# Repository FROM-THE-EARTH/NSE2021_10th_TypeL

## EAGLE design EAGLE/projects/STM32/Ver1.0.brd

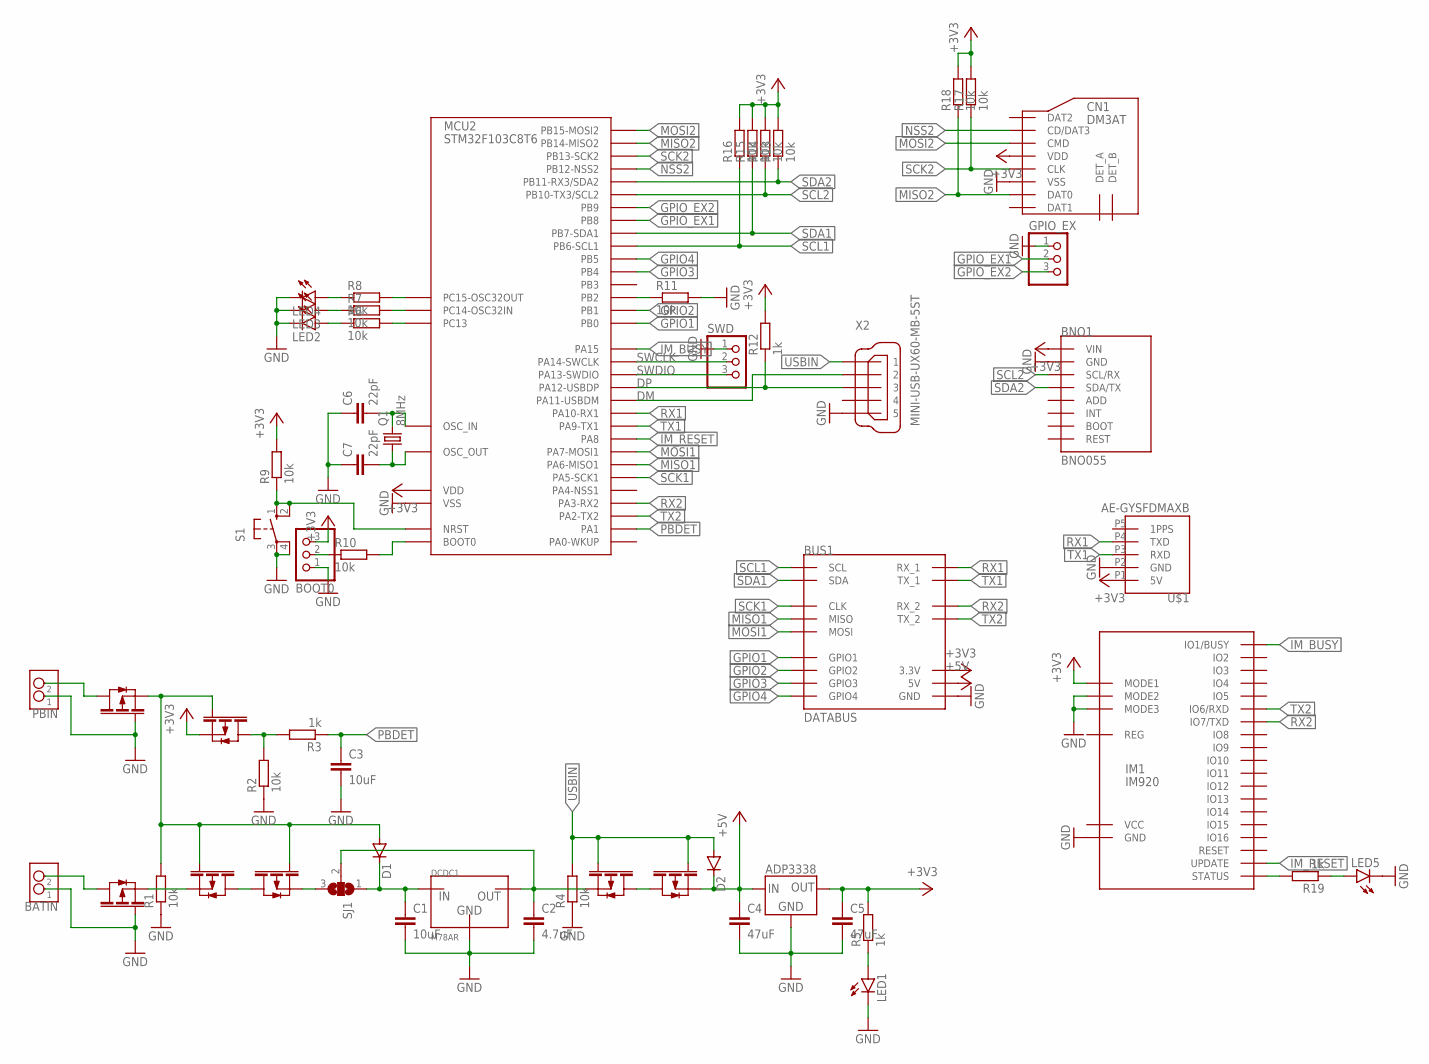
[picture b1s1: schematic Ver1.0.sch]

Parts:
BATIN: S2B-XH-A
BNO1: BNO055
BOOT0: PINHD-1X3/90; 1X03/90
BUS1: DATABUS; 8X2
C1, C3: 10uF; C2012
C2: 4.7uF; C2012
C4, C5: 47uF; C2012
C6, C7: 22pF; C2012
CN1: DM3AT
D1, D2: DIODE-SOD123; SOD123
DCDC1: M78AR
FET1, FET2, FET3, FET4, FET5, FET6, FET7: PCH; SOT-23
GPIO_EX: PINHD-1X3; 1X03
IC1: ADP3338-3.3; SOT-223
IM1: IM920
LED1, LED2, LED3, LED4, LED5: LEDSMT1206; 1206
MCU2: STM32F103C8T6; LQFP48
PBIN: S2B-XH-A
Q1: 8MHz; HC49/S
R1, R2, R4, R6, R7, R8, R9, R10, R11, R13, R14, R15, R16, R17, R18: 10k; R2012
R3, R5, R12, R19: 1k; R2012
S1: 10-XX; B3F-10XX
SJ1: SJ2W; SJ_2
SWD: PINHD-1X3/90; 1X03/90
U$1: AE-GYSFDMAXB
X2: MINI-USB-UX60-MB-5ST; UX60-MB-5ST

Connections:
+3V3: BNO1.P1 (VIN), BOOT0.3, BUS1.P6 (3.3V), CN1.VDD, FET5.P$2, IM1.IO17 (MODE1), MCU2.1 (VDD), MCU2.9 (VDD), MCU2.24 (VDD), MCU2.36 (VDD), MCU2.48 (VDD), R9.2, R12.2, R13.2, R14.2, R15.2, R16.2, R17.2, R18.2, U$1.P1 (5V)
+5V: BUS1.P7 (5V), C4.1, D2.C, FET7.P$2, IC1.3 (IN)
BAT_CON_FET: BATIN.P$2 (2), FET2.P$3
BAT_FET_FET1: FET2.P$2, FET3.P$2
BAT_FET_FET2: FET3.P$3, FET4.P$3
BAT_JMP_DCDC: C1.1, D1.C, DCDC1.P3 (IN), SJ1.1
BOOT0: MCU2.44 (BOOT0), R10.2
BOOT0_R_SEL: BOOT0.2, R10.1
DCDC_FET: C2.1, DCDC1.P1 (OUT), FET6.P$2, SJ1.2
DCDC_FET_FET: FET6.P$3, FET7.P$3
DM: MCU2.32 (PA11-USBDM), X2.2
DP: MCU2.33 (PA12-USBDP), R12.1, X2.3
GND: BATIN.P$1 (1), BNO1.P2 (GND), BOOT0.1, BUS1.P11 (GND), C1.2, C2.2, C3.2, C4.2, C5.2, C6.1, C7.1, CN1.VSS, DCDC1.P2 (GND), FET1.P$1, FET2.P$1, GPIO_EX.1, IC1.4 (GND), IM1.IO18 (MODE2), IM1.IO19 (MODE3), IM1.IO24 (GND), LED1.C, LED2.C, LED3.C, LED4.C, LED5.C, MCU2.8 (VSS), MCU2.23 (VSS), MCU2.35 (VSS), MCU2.47 (VSS), PBIN.P$1 (1), R1.1, R2.1, R4.1, R11.2, S1.3, S1.4 (P1), SWD.1, U$1.P2 (GND), X2.5
GPIO1: BUS1.P3 (GPIO1), MCU2.18 (PB0)
GPIO2: BUS1.P10 (GPIO2), MCU2.19 (PB1)
GPIO3: BUS1.P14 (GPIO3), MCU2.40 (PB4)
GPIO4: BUS1.P15 (GPIO4), MCU2.41 (PB5)
GPIO_EX1: GPIO_EX.2, MCU2.45 (PB8)
GPIO_EX2: GPIO_EX.3, MCU2.46 (PB9)
IM_BUSY: IM1.IO1 (IO1/BUSY), MCU2.38 (PA15)
IM_RESET: IM1.IO20 (UPDATE), MCU2.29 (PA8)
IM_STATUS_LED: LED5.A, R19.1
IM_STATUS_R: IM1.IO21 (STATUS), R19.2
MISO1: BUS1.P12 (MISO), MCU2.16 (PA6-MISO1)
MISO2: CN1.DAT0, MCU2.27 (PB14-MISO2), R18.1
MOSI1: BUS1.P2 (MOSI), MCU2.17 (PA7-MOSI1)
MOSI2: CN1.CMD, MCU2.28 (PB15-MOSI2)
NRST: MCU2.7 (NRST), R9.1, S1.1 (S), S1.2 (S1)
NSS2: CN1.CD/DAT3, MCU2.25 (PB12-NSS2)
OSCI_C: C6.2, MCU2.5 (OSC_IN), Q1.2
OSCO_C: C7.2, MCU2.6 (OSC_OUT), Q1.1
PB2_R: MCU2.20 (PB2), R11.1
PBDET: C3.1, MCU2.11 (PA1), R3.1
PBDET_FET_R: FET5.P$3, R2.2, R3.2
PB_CON_FET: FET1.P$3, PBIN.P$2 (2)
PB_FET_DIO: D1.A, FET1.P$2, FET3.P$1, FET4.P$1, FET5.P$1, R1.2
PB_FET_JMP: FET4.P$2, SJ1.3
PC13_R: MCU2.2 (PC13), R6.2
PC13_R_LED: LED2.A, R6.1
PC14_R: MCU2.3 (PC14-OSC32IN), R7.2
PC14_R_LED: LED3.A, R7.1
PC15_R: MCU2.4 (PC15-OSC32OUT), R8.2
PC15_R_LED: LED4.A, R8.1
POW_R_LED: LED1.A, R5.1
REG_SW: C5.1, IC1.1 (OUT), IC1.2 (OUT), R5.2
RX1: BUS1.P4 (RX_1), MCU2.31 (PA10-RX1), U$1.P4 (TXD)
RX2: BUS1.P9 (RX_2), IM1.IO7 (IO7/TXD), MCU2.13 (PA3-RX2)
SCK1: BUS1.P1 (CLK), MCU2.15 (PA5-SCK1)
SCK2: CN1.CLK, MCU2.26 (PB13-SCK2), R17.1
SCL1: BUS1.P0 (SCL), MCU2.42 (PB6-SCL1), R16.1
SCL2: BNO1.P3 (SCL/RX), MCU2.21 (PB10-TX3/SCL2), R14.1
SDA1: BUS1.P13 (SDA), MCU2.43 (PB7-SDA1), R15.1
SDA2: BNO1.P4 (SDA/TX), MCU2.22 (PB11-RX3/SDA2), R13.1
SWCLK: MCU2.37 (PA14-SWCLK), SWD.2
SWDIO: MCU2.34 (PA13-SWDIO), SWD.3
TX1: BUS1.P5 (TX_1), MCU2.30 (PA9-TX1), U$1.P3 (RXD)
TX2: BUS1.P8 (TX_2), IM1.IO6 (IO6/RXD), MCU2.12 (PA2-TX2)
USBIN: D2.A, FET6.P$1, FET7.P$1, R4.2, X2.1

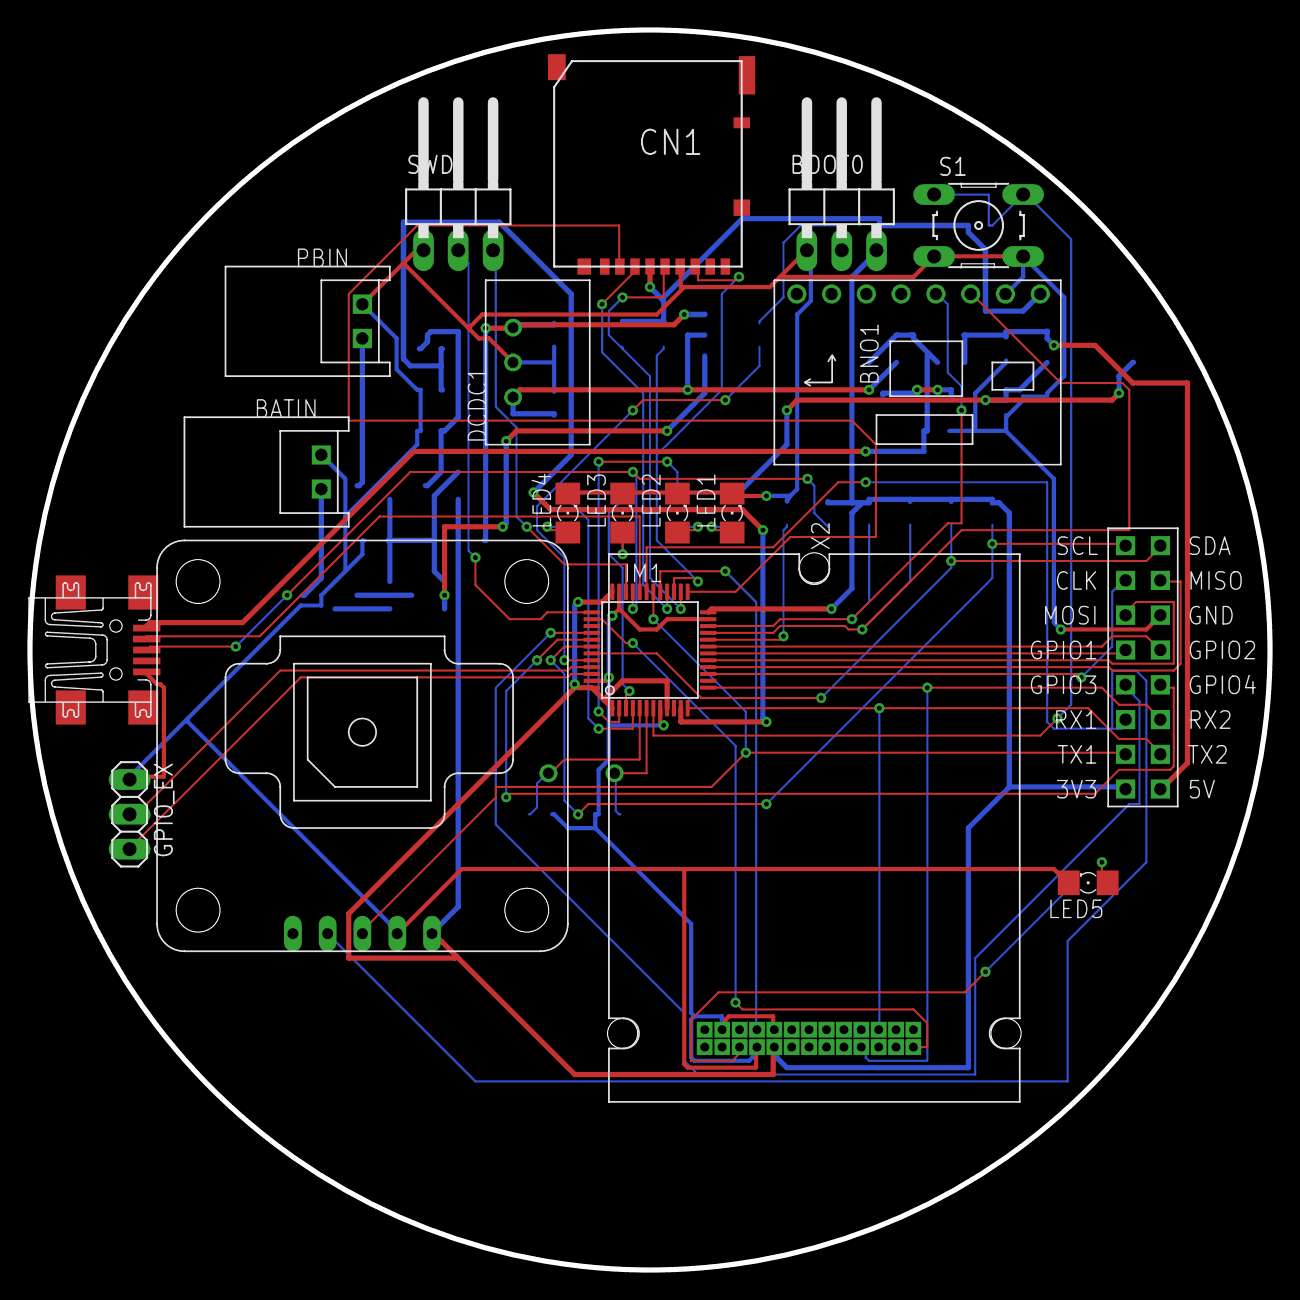
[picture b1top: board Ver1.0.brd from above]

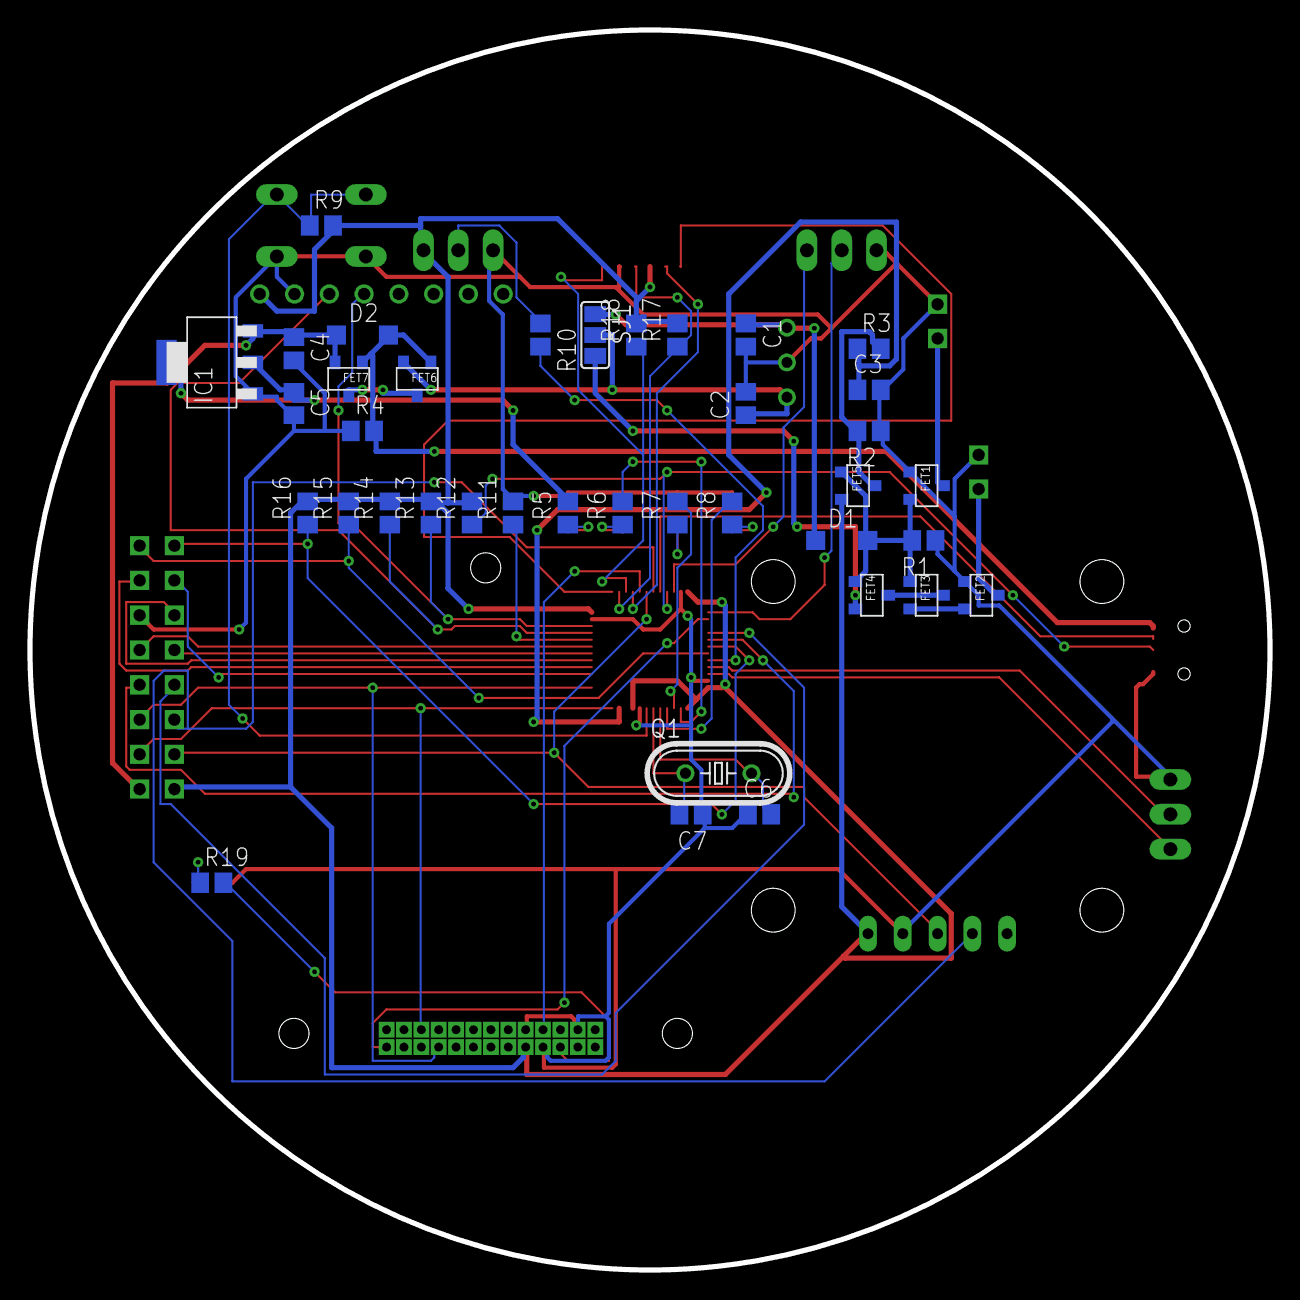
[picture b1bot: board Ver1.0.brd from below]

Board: 2 copper layers, 90.6 x 90.6 mm, 57 parts (38 on the bottom side), 58 nets.

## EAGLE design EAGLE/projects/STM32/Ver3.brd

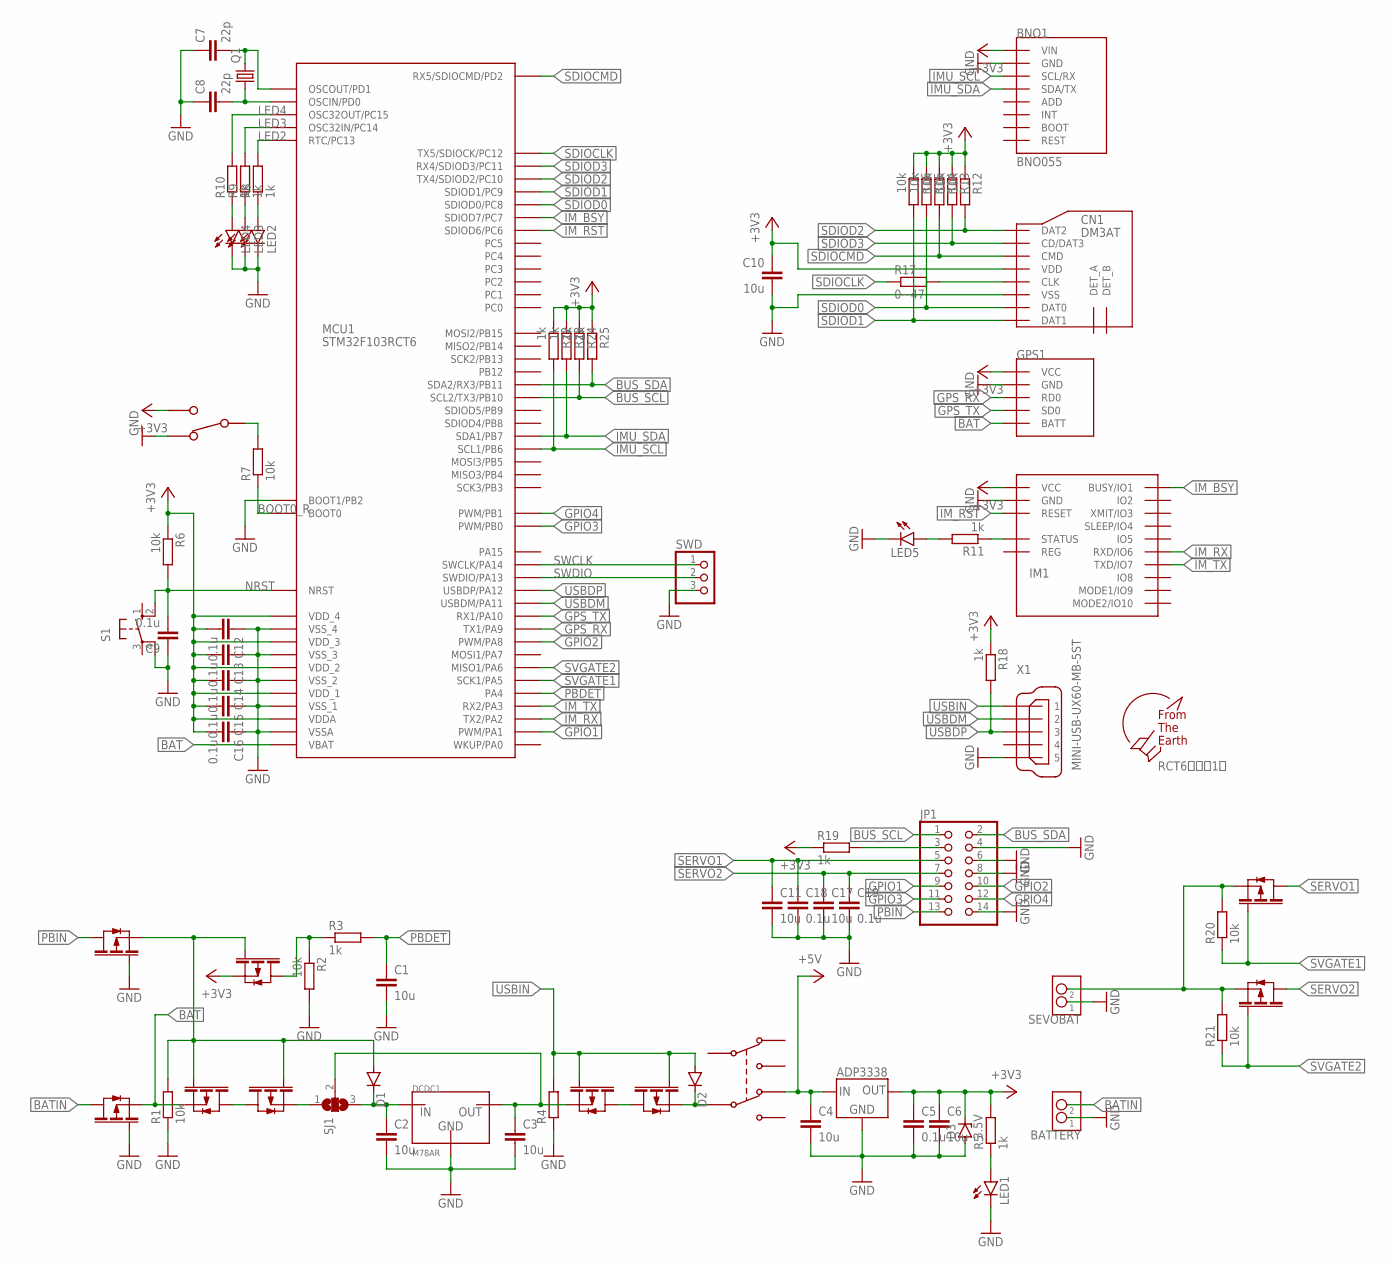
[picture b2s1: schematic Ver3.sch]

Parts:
BATTERY: S2B-XH-A
BNO1: BNO055
C1, C2, C3, C4, C6, C10, C11, C17: 10u; C0805
C5, C9, C12, C13, C14, C15, C16, C18, C19: 0.1u; C0805
C7, C8: 22p; C0805
CN1: DM3AT
D1, D2: DIODE-SOD123; SOD123
D3: 3.5V; SMB
DCDC1: M78AR
FET1, FET2, FET3, FET4, FET5, FET6, FET7, FET8, FET9: PCH; SOT-23
GPS1: GPS-54D
IC1: ADP3338-3.3; SOT-223
IM1: IM920C
JP1: PINHD-2X7; 2X07
LED1, LED2, LED3, LED4, LED5: LEDSML0603; SML0603
MCU1: STM32F103RCT6; LQFP64
Q1: CRYSTALHC49S; HC49/S
R1, R2, R6, R7, R12, R13, R14, R15, R16, R20, R21: 10k; R0603
R3, R5, R8, R9, R10, R11, R18, R19, R22, R23, R24, R25: 1k; R0603
R4: R-EU_R0603; R0603
R17: 0~47; R0603
RCT6用試作1号: F.T.E.LOGO; LOGO
S1: 10-XX; B3F-10XX
SEVOBAT: S2B-XH-A
SJ1: SJ2W; SJ_2
SWD: PINHD-1X3/90; 1X03/90
U$2: SSSS213202; SMD_6P
U$3: MSS22D18
X1: MINI-USB-UX60-MB-5ST; UX60-MB-5ST

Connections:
3V3_R: JP1.3, R19.2
+3V3: BNO1.P1 (VIN), C5.1, C6.1, C10.1, C12.2, C13.2, C14.2, C15.2, C16.2, CN1.VDD, D3.C, FET5.P$2, GPS1.VCC, IC1.1 (OUT), IC1.2 (OUT), IM1.$P17 (VCC), MCU1.P$13 (VDDA), MCU1.P$19 (VDD_4), MCU1.P$32 (VDD_1), MCU1.P$48 (VDD_2), MCU1.P$64 (VDD_3), R5.2, R6.1, R12.1, R13.1, R14.1, R15.1, R16.1, R18.1, R19.1, R22.1, R23.1, R24.1, R25.1, U$2.P$0 (PD1), U$2.P$5 (PD1)
+5V: C4.1, IC1.3 (IN), U$3.P$2
BAT: FET1.P$2, FET3.P$2, GPS1.BATT, MCU1.P$1 (VBAT)
BATIN: BATTERY.P$2 (2), FET1.P$3
BAT_FET2FET: FET2.P$3, FET3.P$3
BAT_FET2JMP: FET2.P$2, SJ1.1
BOOT0_PH: R7.2, U$2.P$1 (PD2), U$2.P$4 (PD2)
BOOT0_R: MCU1.P$60 (BOOT0), R7.1
BUS_SCL: JP1.1, MCU1.P$29 (SCL2/TX3/PB10), R24.2
BUS_SDA: JP1.2, MCU1.P$30 (SDA2/RX3/PB11), R25.2
DCDCIN: C2.1, D1.C, DCDC1.P3 (IN), SJ1.3
GND: BATTERY.P$1 (1), BNO1.P2 (GND), C1.2, C2.2, C3.2, C4.2, C5.2, C6.2, C7.1, C8.1, C9.1, C10.2, C11.2, C12.1, C13.1, C14.1, C15.1, C16.1, C17.2, C18.2, C19.2, CN1.VSS, D3.A, DCDC1.P2 (GND), FET1.P$1, FET4.P$1, GPS1.GND, IC1.4 (GND), IM1.$P18 (GND), JP1.4, JP1.6, JP1.8, JP1.14, LED1.C, LED2.C, LED3.C, LED4.C, LED5.C, MCU1.P$12 (VSSA), MCU1.P$18 (VSS_4), MCU1.P$28 (BOOT1/PB2), MCU1.P$31 (VSS_1), MCU1.P$47 (VSS_2), MCU1.P$63 (VSS_3), R1.1, R2.2, R4.1, S1.4 (P1), SEVOBAT.P$1 (1), SWD.3, U$2.P$2 (PD3), U$2.P$3 (PD3), X1.5
GPIO1: JP1.9, MCU1.P$15 (PWM/PA1)
GPIO2: JP1.10, MCU1.P$41 (PWM/PA8)
GPIO3: JP1.11, MCU1.P$26 (PWM/PB0)
GPIO4: JP1.12, MCU1.P$27 (PWM/PB1)
GPS_RX: GPS1.RD0, MCU1.P$42 (TX1/PA9)
GPS_TX: GPS1.SD0, MCU1.P$43 (RX1/PA10)
IMU_SCL: BNO1.P3 (SCL/RX), MCU1.P$58 (SCL1/PB6), R22.2
IMU_SDA: BNO1.P4 (SDA/TX), MCU1.P$59 (SDA1/PB7), R23.2
IM_BSY: IM1.$P1 (BUSY/IO1), MCU1.P$38 (SDIOD7/PC7)
IM_LED: LED5.A, R11.2
IM_R: IM1.$P15 (STATUS), R11.1
IM_RST: IM1.$P19 (RESET), MCU1.P$37 (SDIOD6/PC6)
IM_RX: IM1.$P6 (RXD/IO6), MCU1.P$16 (TX2/PA2)
IM_TX: IM1.$P7 (TXD/IO7), MCU1.P$17 (RX2/PA3)
LED2: MCU1.P$2 (RTC/PC13), R8.2
LED2R: LED2.A, R8.1
LED3: MCU1.P$3 (OSC32IN/PC14), R9.2
LED3R: LED3.A, R9.1
LED4: MCU1.P$4 (OSC32OUT/PC15), R10.2
LED4R: LED4.A, R10.1
NRST: C9.2, MCU1.P$7 (NRST), R6.2, S1.2 (S1)
OSCIN: C8.2, MCU1.P$5 (OSCIN/PD0), Q1.1
OSCOUT: C7.2, MCU1.P$6 (OSCOUT/PD1), Q1.2
PBDET: C1.1, MCU1.P$20 (PA4), R3.2
PBIN: FET4.P$3, JP1.13
PB_ARV2GATES: D1.A, FET2.P$1, FET3.P$1, FET4.P$2, FET5.P$1, R1.2
PB_FET2R: FET5.P$3, R2.1, R3.1
PWR_SWC: D2.C, FET7.P$2, U$3.P$1
REG_DCDC2FET: C3.1, DCDC1.P1 (OUT), FET6.P$2, SJ1.2
REG_FET2FET: FET6.P$3, FET7.P$3
REG_R2LED: LED1.A, R5.1
SDIOCLK: MCU1.P$53 (TX5/SDIOCK/PC12), R17.1
SDIOCLK_R: CN1.CLK, R17.2
SDIOCMD: CN1.CMD, MCU1.P$54 (RX5/SDIOCMD/PD2), R14.2
SDIOD0: CN1.DAT0, MCU1.P$39 (SDIOD0/PC8), R15.2
SDIOD1: CN1.DAT1, MCU1.P$40 (SDIOD1/PC9), R16.2
SDIOD2: CN1.DAT2, MCU1.P$51 (TX4/SDIOD2/PC10), R12.2
SDIOD3: CN1.CD/DAT3, MCU1.P$52 (RX4/SDIOD3/PC11), R13.2
SERVO1: C11.1, C18.1, FET8.P$3, JP1.5
SERVO2: C17.1, C19.1, FET9.P$3, JP1.7
SVGATE1: FET8.P$1, MCU1.P$21 (SCK1/PA5), R20.1
SVGATE2: FET9.P$1, MCU1.P$22 (MISO1/PA6), R21.1
SVIN: FET8.P$2, FET9.P$2, R20.2, R21.2, SEVOBAT.P$2 (2)
SWCLK: MCU1.P$49 (SWCLK/PA14), SWD.1
SWDIO: MCU1.P$46 (SWDIO/PA13), SWD.2
USBDM: MCU1.P$44 (USBDM/PA11), X1.2
USBDP: MCU1.P$45 (USBDP/PA12), R18.2, X1.3
USBIN: D2.A, FET6.P$1, FET7.P$1, R4.2, X1.1

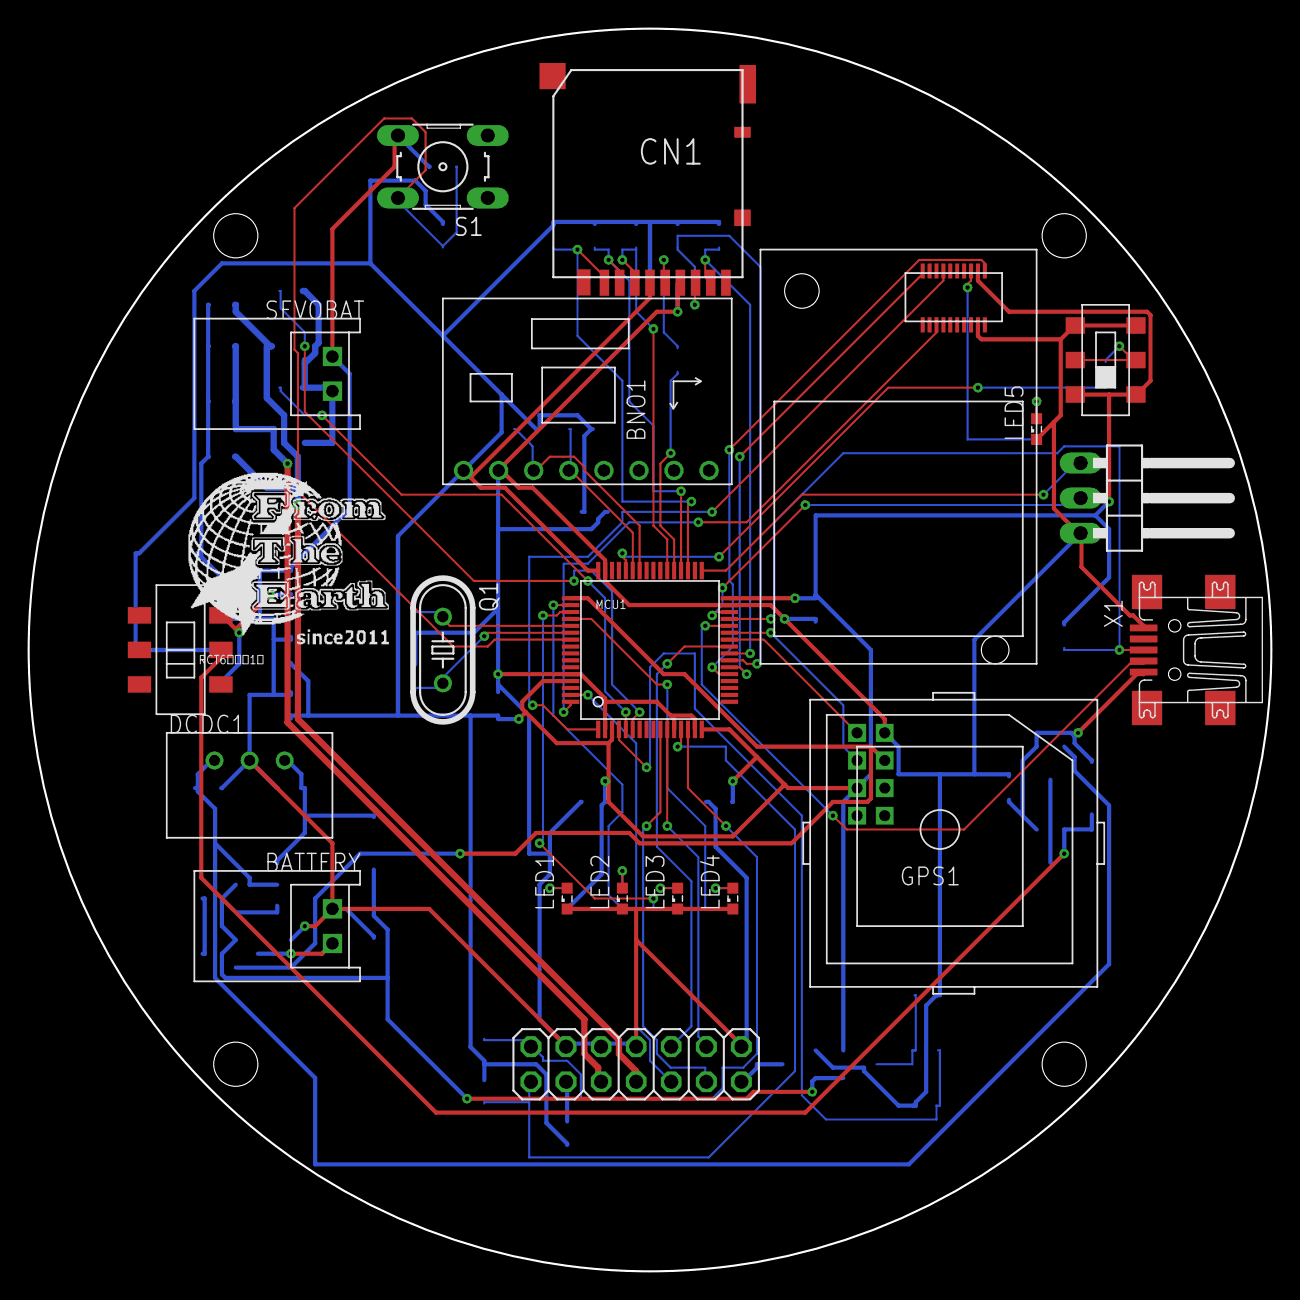
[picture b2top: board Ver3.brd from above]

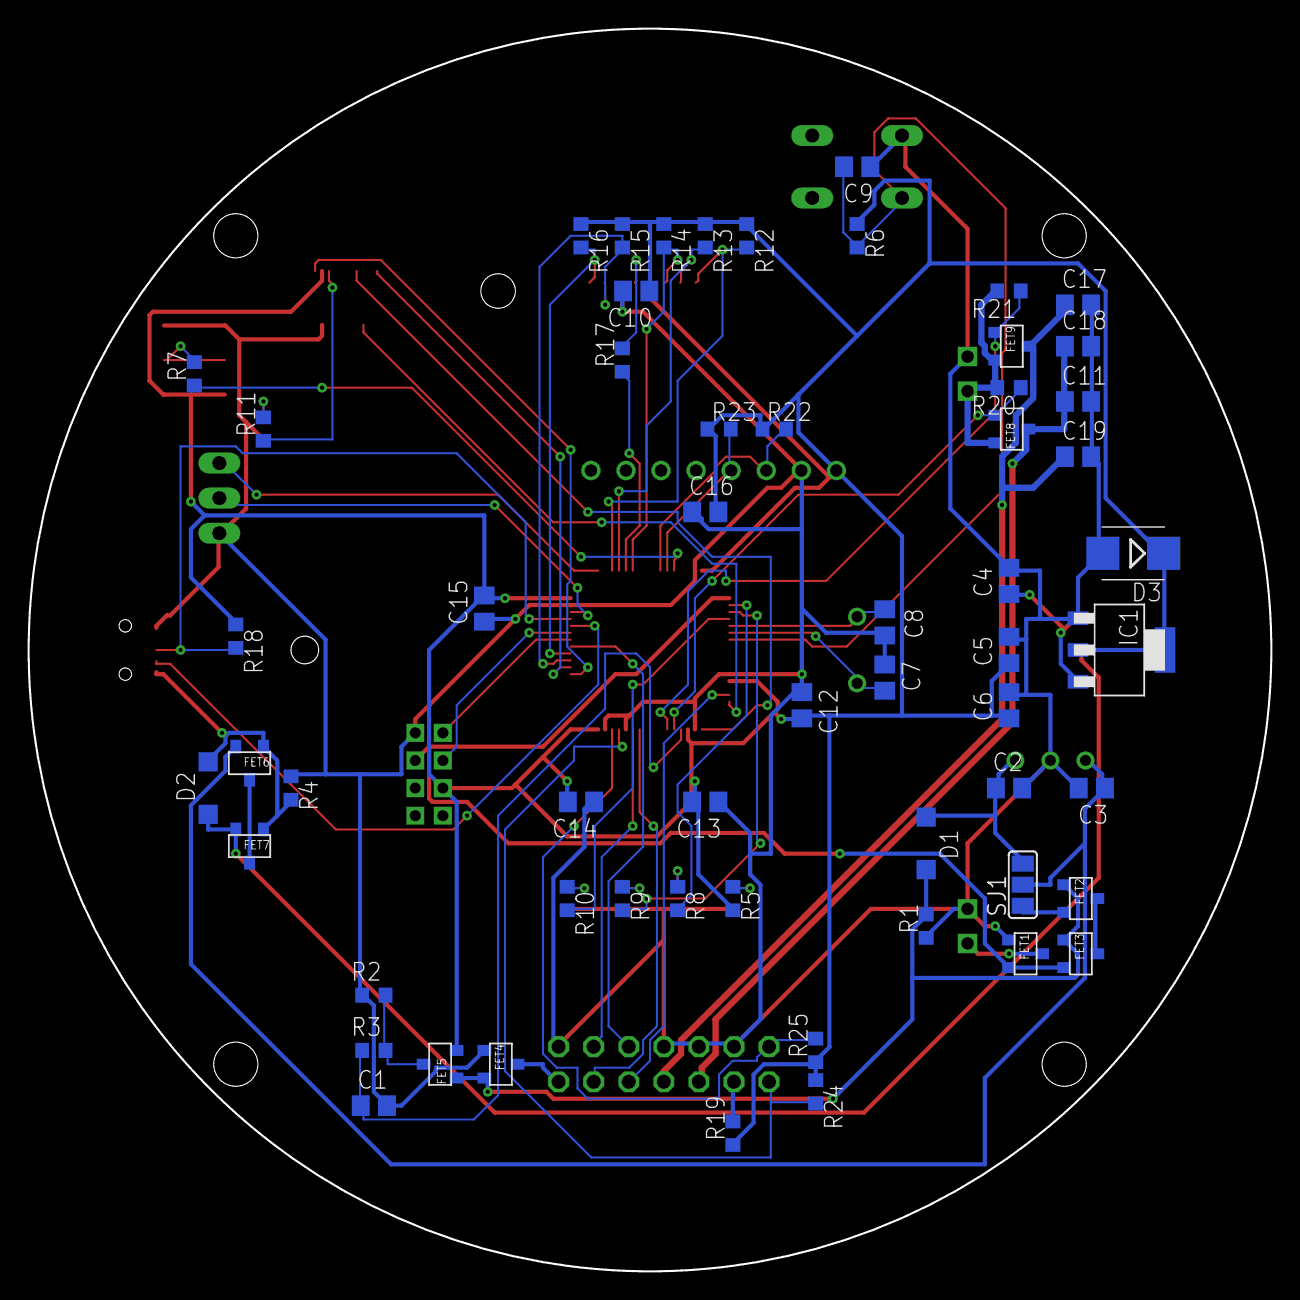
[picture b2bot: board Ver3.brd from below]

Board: 2 copper layers, 90.0 x 90.0 mm, 79 parts (58 on the bottom side), 61 nets.

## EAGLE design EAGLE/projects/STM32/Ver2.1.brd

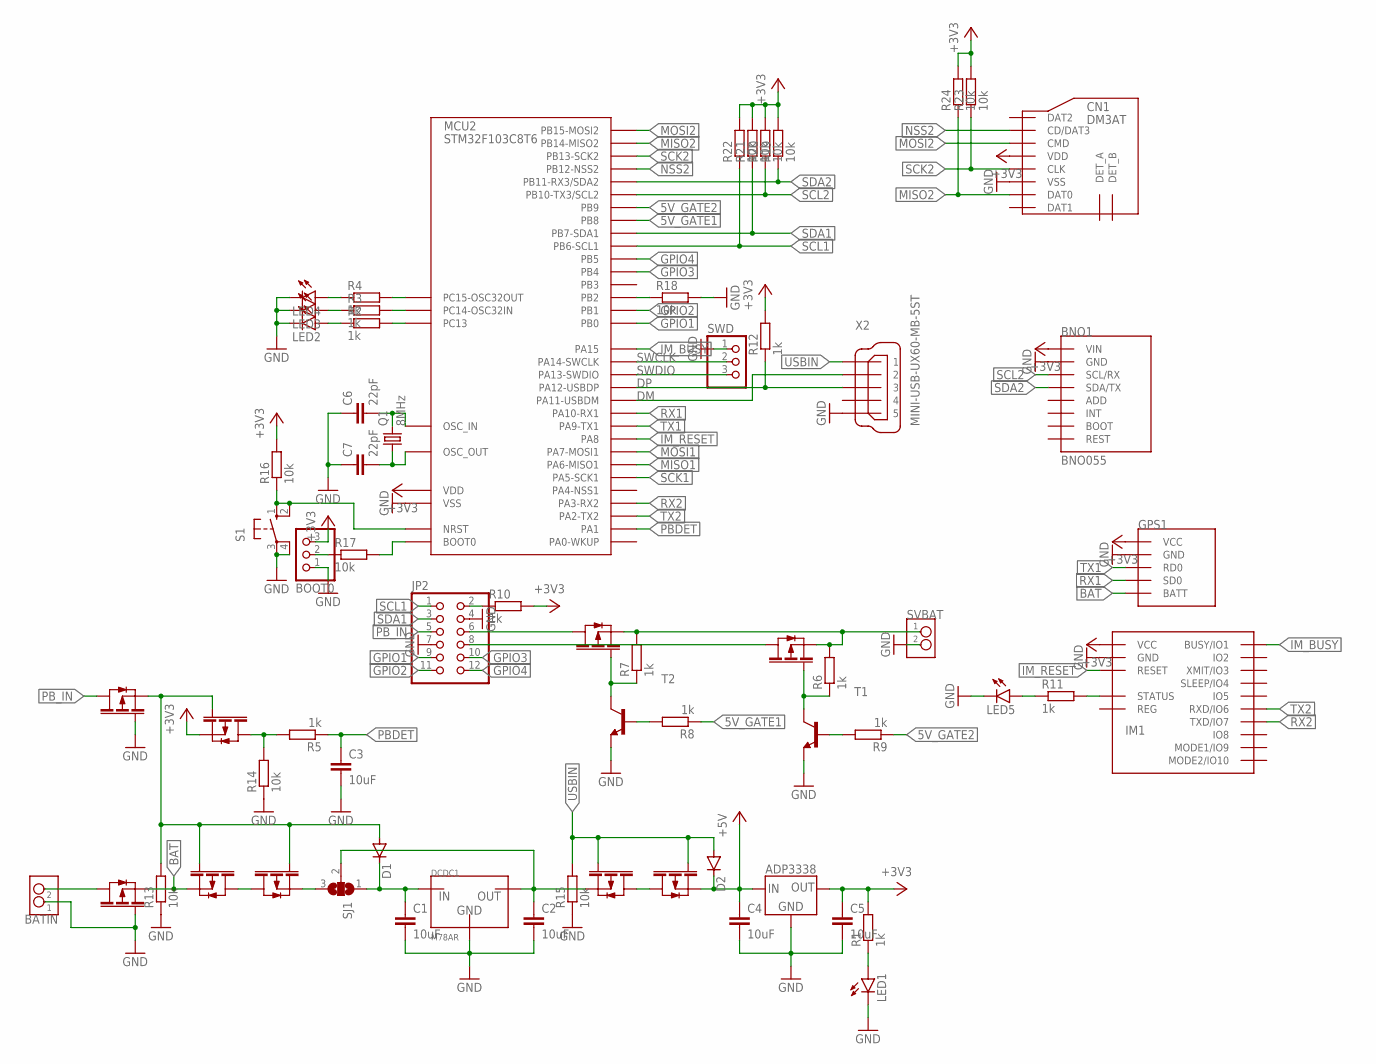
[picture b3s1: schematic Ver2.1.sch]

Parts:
BATIN: S2B-XH-A
BNO1: BNO055
BOOT0: PINHD-1X3; 1X03
C1, C2, C3, C4, C5: 10uF; C2012
C6, C7: 22pF; C2012
CN1: DM3AT
D1, D2: DIODE-SOD123; SOD123
DCDC1: M78AR
FET1, FET2, FET3, FET4, FET5, FET6, FET7, FET8, FET9: PCH; SOT-23
GPS1: GPS-54D
IC1: ADP3338-3.3; SOT-223
IM1: IM920C
JP2: PINHD-2X6; 2X06
LED1, LED2, LED3, LED4, LED5: LEDSMT1206; 1206
MCU2: STM32F103C8T6; LQFP48
Q1: 8MHz; HC49/S
R1, R2, R3, R4, R5, R6, R7, R8, R9, R10, R11, R12: 1k; R2012
R13, R14, R15, R16, R17, R18, R19, R20, R21, R22, R23, R24: 10k; R2012
S1: 10-XX; B3F-10XX
SJ1: SJ2W; SJ_2
SVBAT: S2B-XH-A
SWD: PINHD-1X3; 1X03
T1, T2: -NPN-SOT23-EBC; SOT23-EBC
X2: MINI-USB-UX60-MB-5ST; UX60-MB-5ST

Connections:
3V3_R_CON: JP2.2, R10.1
5V_CL1: R8.2, T2.B
5V_CL2: R9.2, T1.B
5V_FET1_CON: FET8.P$3, JP2.6
5V_FET2_CON: FET9.P$3, JP2.8
5V_GATE1: MCU2.45 (PB8), R8.1
5V_GATE2: MCU2.46 (PB9), R9.1
5V_TR1: FET8.P$1, R7.1, T2.C
5V_TR2: FET9.P$1, R6.1, T1.C
+3V3: BNO1.P1 (VIN), BOOT0.3, C5.1, CN1.VDD, FET5.P$2, GPS1.VCC, IC1.1 (OUT), IC1.2 (OUT), IM1.$P17 (VCC), MCU2.1 (VDD), MCU2.9 (VDD), MCU2.24 (VDD), MCU2.36 (VDD), MCU2.48 (VDD), R1.2, R10.2, R12.2, R16.2, R19.2, R20.2, R21.2, R22.2, R23.2, R24.2
+5V: C4.1, D2.C, FET7.P$2, IC1.3 (IN)
BAT: FET2.P$2, FET3.P$2, GPS1.BATT
BAT_CON_FET: BATIN.P$2 (2), FET2.P$3
BAT_FET_FET2: FET3.P$3, FET4.P$3
BAT_JMP_DCDC: C1.1, D1.C, DCDC1.P3 (IN), SJ1.1
BOOT0: MCU2.44 (BOOT0), R17.2
BOOT0_R_SEL: BOOT0.2, R17.1
DCDC_FET: C2.1, DCDC1.P1 (OUT), FET6.P$2, SJ1.2
DCDC_FET_FET: FET6.P$3, FET7.P$3
DM: MCU2.32 (PA11-USBDM), X2.2
DP: MCU2.33 (PA12-USBDP), R12.1, X2.3
GND: BATIN.P$1 (1), BNO1.P2 (GND), BOOT0.1, C1.2, C2.2, C3.2, C4.2, C5.2, C6.1, C7.1, CN1.VSS, DCDC1.P2 (GND), FET1.P$1, FET2.P$1, GPS1.GND, IC1.4 (GND), IM1.$P18 (GND), JP2.4, JP2.7, LED1.C, LED2.C, LED3.C, LED4.C, LED5.C, MCU2.8 (VSS), MCU2.23 (VSS), MCU2.35 (VSS), MCU2.47 (VSS), R13.1, R14.1, R15.1, R18.2, S1.3, S1.4 (P1), SVBAT.P$2 (2), SWD.1, T1.E, T2.E, X2.5
GPIO1: JP2.9, MCU2.18 (PB0)
GPIO2: JP2.11, MCU2.19 (PB1)
GPIO3: JP2.10, MCU2.40 (PB4)
GPIO4: JP2.12, MCU2.41 (PB5)
IM_BUSY: IM1.$P1 (BUSY/IO1), MCU2.38 (PA15)
IM_RESET: IM1.$P19 (RESET), MCU2.29 (PA8)
IM_STATUS_LED: LED5.A, R11.1
IM_STATUS_R: IM1.$P15 (STATUS), R11.2
MISO1: MCU2.16 (PA6-MISO1)
MISO2: CN1.DAT0, MCU2.27 (PB14-MISO2), R24.1
MOSI1: MCU2.17 (PA7-MOSI1)
MOSI2: CN1.CMD, MCU2.28 (PB15-MOSI2)
NRST: MCU2.7 (NRST), R16.1, S1.1 (S), S1.2 (S1)
NSS2: CN1.CD/DAT3, MCU2.25 (PB12-NSS2)
OSCI_C: C6.2, MCU2.5 (OSC_IN), Q1.2
OSCO_C: C7.2, MCU2.6 (OSC_OUT), Q1.1
PB2_R: MCU2.20 (PB2), R18.1
PBDET: C3.1, MCU2.11 (PA1), R5.1
PBDET_FET_R: FET5.P$3, R5.2, R14.2
PB_FET_DIO: D1.A, FET1.P$2, FET3.P$1, FET4.P$1, FET5.P$1, R13.2
PB_FET_JMP: FET4.P$2, SJ1.3
PB_IN: FET1.P$3, JP2.5
PC13_R: MCU2.2 (PC13), R2.2
PC13_R_LED: LED2.A, R2.1
PC14_R: MCU2.3 (PC14-OSC32IN), R3.2
PC14_R_LED: LED3.A, R3.1
PC15_R: MCU2.4 (PC15-OSC32OUT), R4.2
PC15_R_LED: LED4.A, R4.1
POW_R_LED: LED1.A, R1.1
RX1: GPS1.SD0, MCU2.31 (PA10-RX1)
RX2: IM1.$P7 (TXD/IO7), MCU2.13 (PA3-RX2)
SCK1: MCU2.15 (PA5-SCK1)
SCK2: CN1.CLK, MCU2.26 (PB13-SCK2), R23.1
SCL1: JP2.1, MCU2.42 (PB6-SCL1), R22.1
SCL2: BNO1.P3 (SCL/RX), MCU2.21 (PB10-TX3/SCL2), R20.1
SDA1: JP2.3, MCU2.43 (PB7-SDA1), R21.1
SDA2: BNO1.P4 (SDA/TX), MCU2.22 (PB11-RX3/SDA2), R19.1
SVBAT_IN: FET8.P$2, FET9.P$2, R6.2, R7.2, SVBAT.P$1 (1)
SWCLK: MCU2.37 (PA14-SWCLK), SWD.2
SWDIO: MCU2.34 (PA13-SWDIO), SWD.3
TX1: GPS1.RD0, MCU2.30 (PA9-TX1)
TX2: IM1.$P6 (RXD/IO6), MCU2.12 (PA2-TX2)
USBIN: D2.A, FET6.P$1, FET7.P$1, R15.2, X2.1

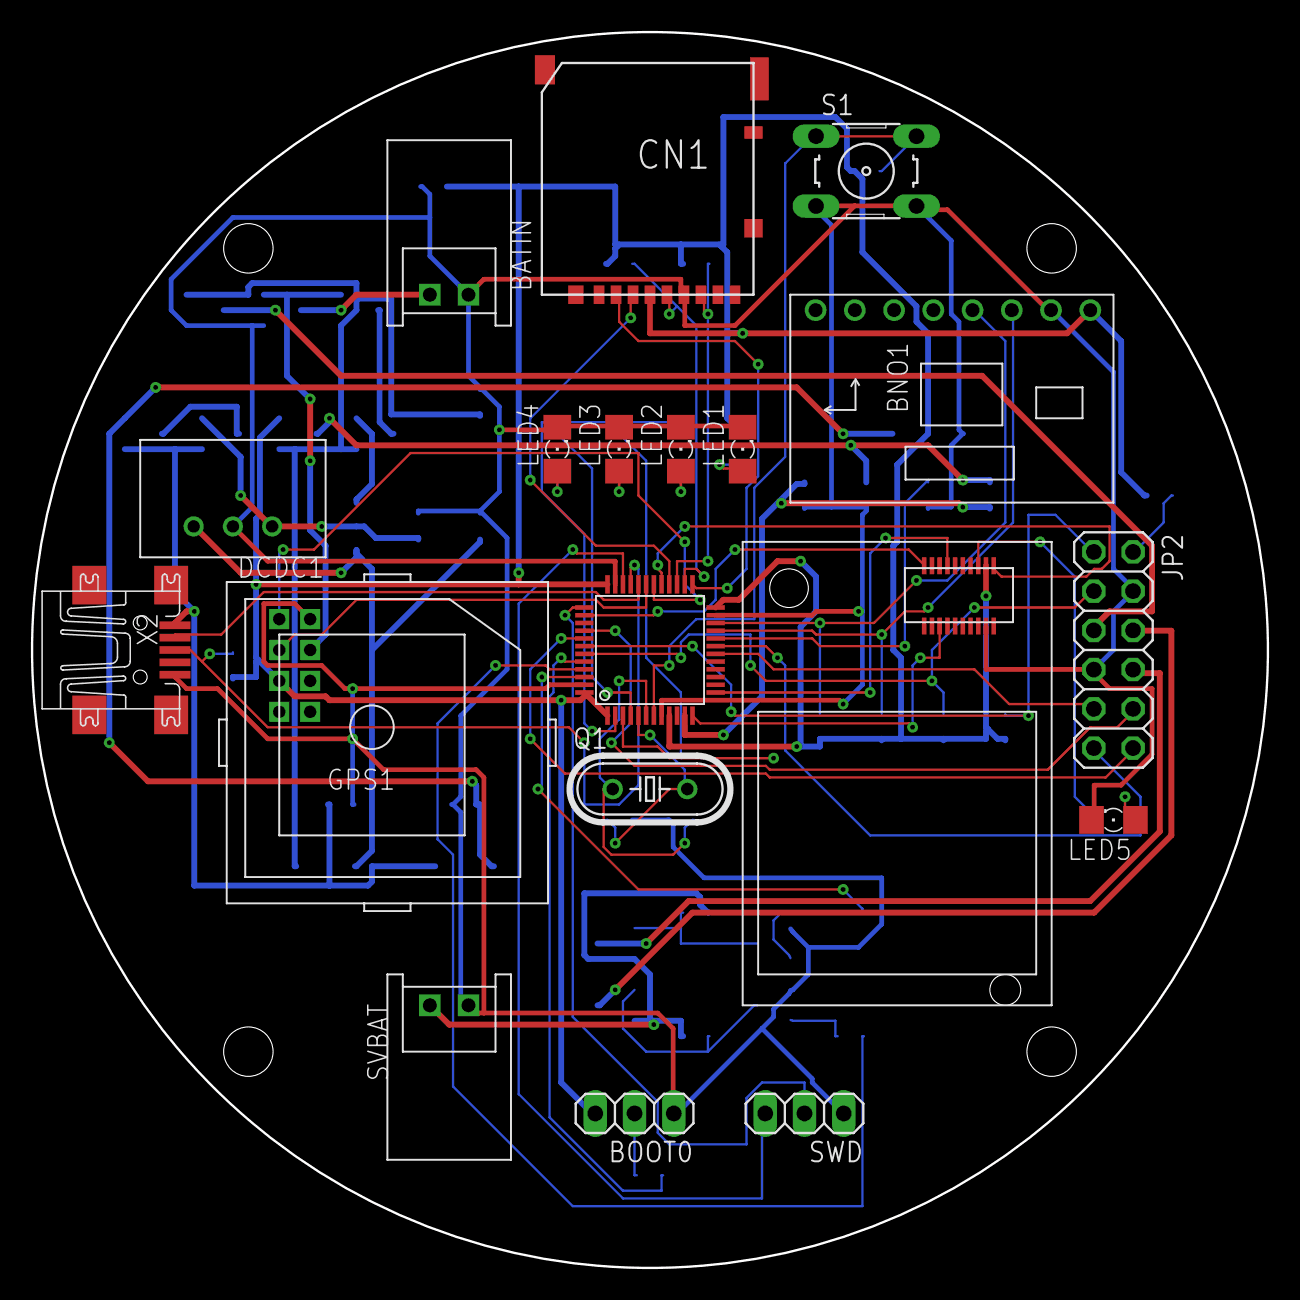
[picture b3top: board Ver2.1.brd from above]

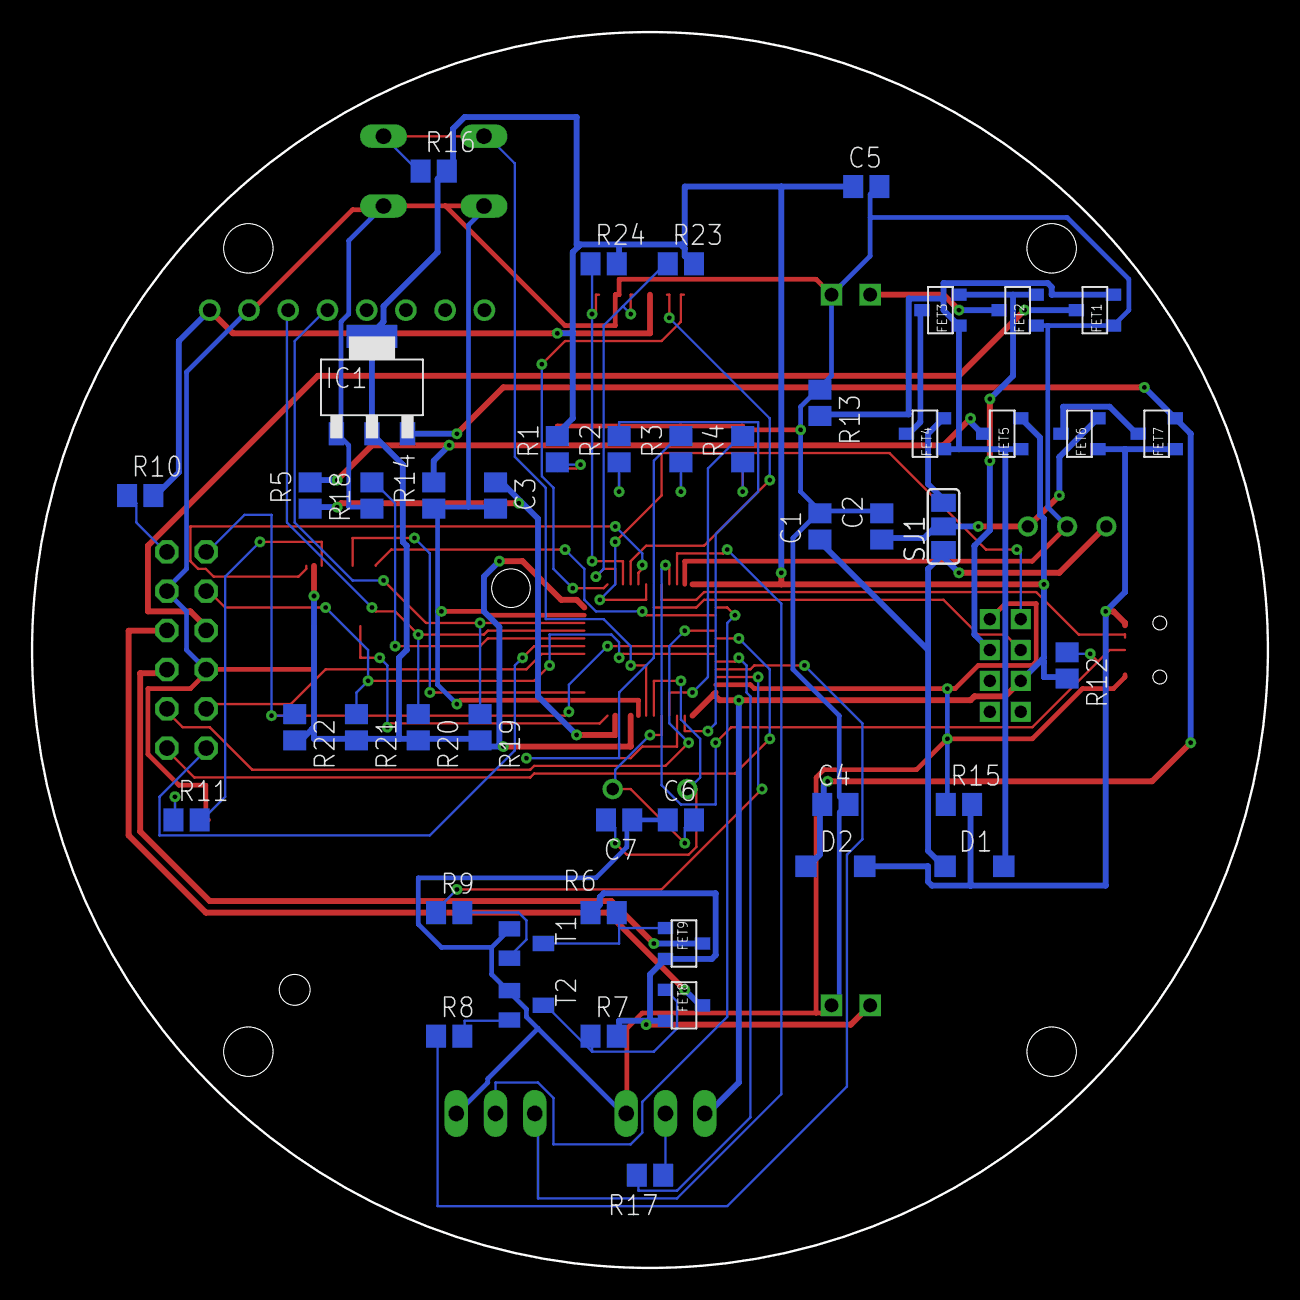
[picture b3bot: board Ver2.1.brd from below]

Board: 2 copper layers, 80.0 x 80.0 mm, 65 parts (46 on the bottom side), 62 nets.
